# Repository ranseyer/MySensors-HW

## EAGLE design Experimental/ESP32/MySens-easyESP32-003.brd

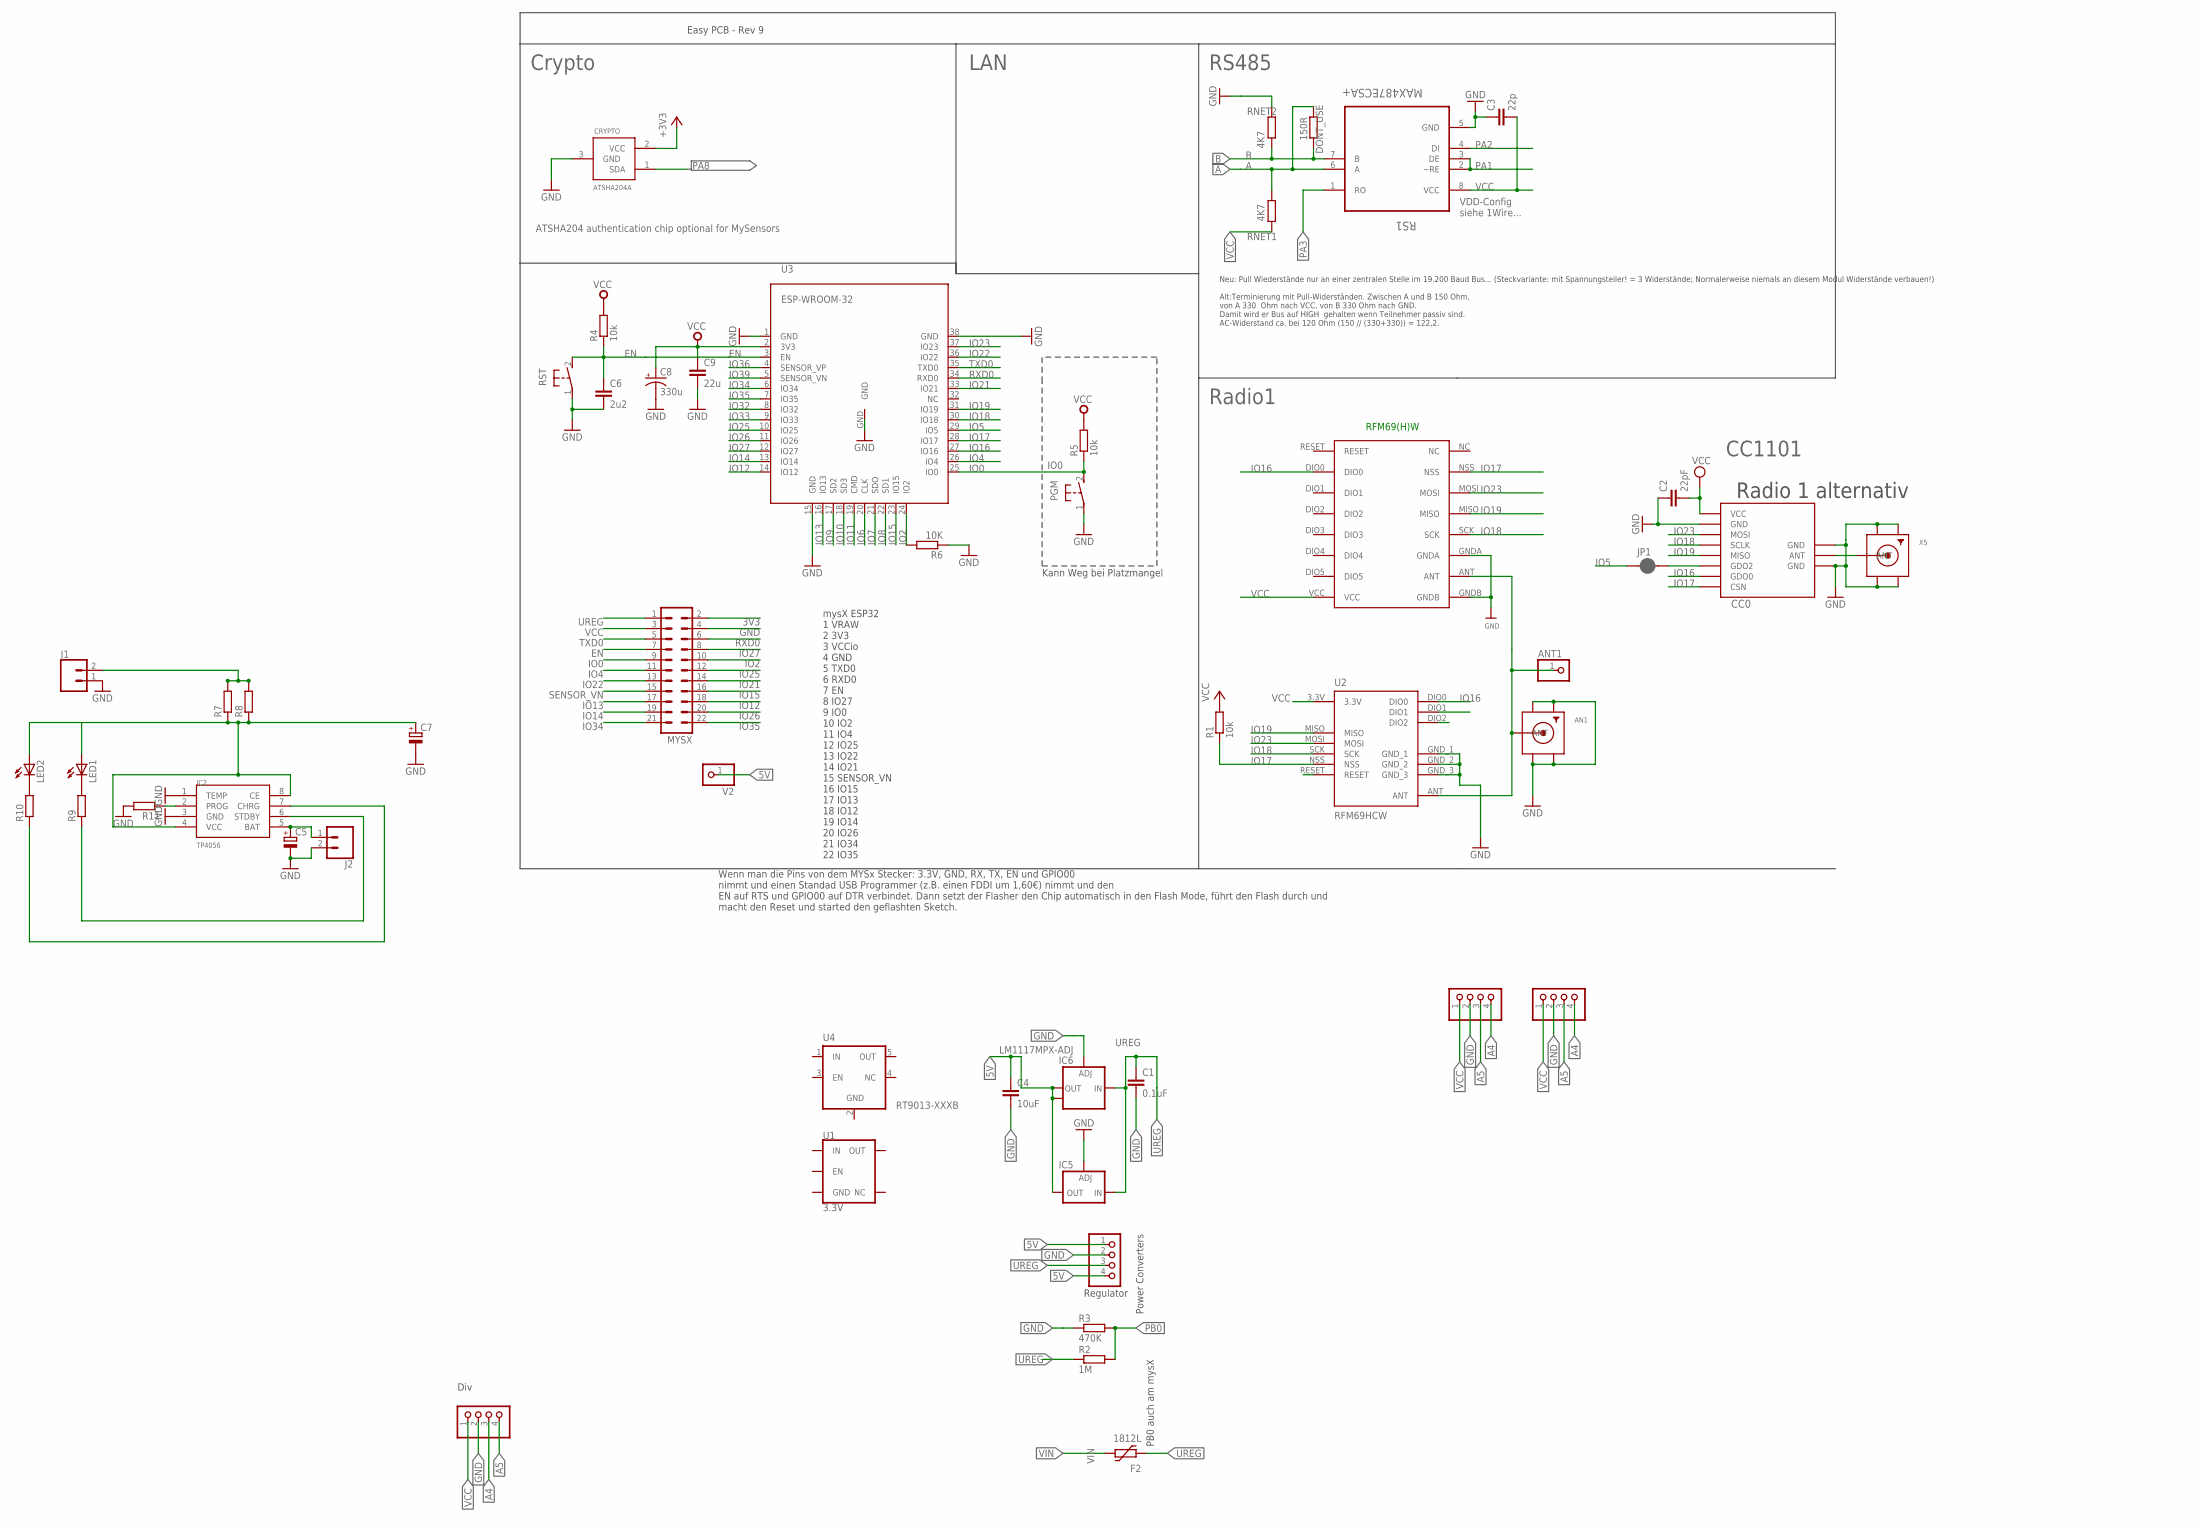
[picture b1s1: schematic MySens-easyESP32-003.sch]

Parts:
AN1: SMACONNECTOR_EDGE; SMA_EDGELAUNCH
ANT1: PINHD-1X1; 1X01
BH1750: PINHD-1X04_2.54-S; 1X04-S
C1: 0.1uF; C1206
C2: 22pF; C0805
C3: 22p; C0805
C4: 10uF; C1210
C5, C7: CPOL-EUE2.5-7; E2,5-7
C6: 2u2; C0603
C8: 330u; VISHAY_C
C9: 22u; 0805
CC0: CC1101; CC1101_MODULE1_SMD
CRYPTO: ATSHA204A; SOT23
DONT_USE: 150R; R0805
F2: 1812L
I2C-1, I2C-2: PINHD-1X04_2.54-S; 1X04-S
IC2: TP4056; SOP-8
IC5: LD117ADT50TR; DPACK
IC6: LM1117MPX-ADJ; SOT223
J1, J2: CONN_02PTH4; 1X02_XTRA_BIG
JP1: JUMPER-SMT_2_NC_PASTE_NO-SILK; SMT-JUMPER_2_NC_PASTE_NO-SILK
LED1, LED2: LED5MM
MYSX: MA11-2
PGM: DTSM-3
R1: 10k; M0805
R2: 1M; R0805
R3: 470K; R0805
R4, R5: 10k; R0603
R6: 10K; R0603
R7, R8, R9, R10, R11: R-EU_R1206; R1206
RFM69W1: RFM69HW; RFM
RNET1, RNET2: 4K7; R0805
RS1: MAX487ECSA+; SOIC127P600X175-8N
RST: DTSM-3
STEPDWN: PINHD-1X04_2.54-S; 1X04-S
U1: 3.3V; SOT23-5
U2: RFM69HCW; RFM69HCW-XXXS2
U3: ESP-WROOM-32
U4: RT9013-XXXB; SOT23-5
V2: PINHD-1X1; 1X01
X5: SMACONNECTOR_EDGE; SMA_EDGELAUNCH

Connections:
3V3: CRYPTO.2 (VCC), MYSX.2
5V: C4.1, IC5.4 (OUT), IC6.2 (OUT), IC6.TAB (OUT1), STEPDWN.1, STEPDWN.4, V2.1
A: DONT_USE.1, RNET1.2, RS1.6 (A)
A4: BH1750.4, I2C-1.4, I2C-2.3
A5: BH1750.3, I2C-1.3, I2C-2.4
ANT0: CC0.ANT, X5.P (ANT)
ANT1: AN1.P (ANT), ANT1.1, RFM69W1.ANT, U2.ANT
B: DONT_USE.2, RNET2.1, RS1.7 (B)
EN: C6.1, MYSX.7, R4.1, RST.2, U3.3 (EN)
GND: AN1.GND@1 (GND4), AN1.GND@2 (GND3), AN1.GND@3 (GND2), AN1.GND@4 (GND1), BH1750.2, C1.2, C2.1, C3.1, C4.2, C5.-, C6.2, C7.-, C8.-, C9.2, CC0.GND@0 (GND), CC0.GND@1 (GND), CC0.GND@2 (GND), CRYPTO.3 (GND), I2C-1.2, I2C-2.2, IC2.1 (TEMP), IC2.3 (GND), IC5.1 (ADJ), IC6.1 (ADJ), J1.1, J2.2, MYSX.4, PGM.1, R3.1, R6.1, R11.2, RFM69W1.GNDA, RFM69W1.GNDB, RNET2.2, RS1.5 (GND), RST.1, STEPDWN.2, U2.GND_1, U2.GND_2, U2.GND_3, U3.1 (GND), U3.15 (GND), U3.38 (GND), U3.GND, U4.2 (GND), X5.GND@1 (GND4), X5.GND@2 (GND3), X5.GND@3 (GND2), X5.GND@4 (GND1)
IO0: MYSX.9, PGM.2, R5.1, U3.25 (IO0)
IO2: MYSX.10, R6.2, U3.24 (IO2)
IO4: MYSX.11, U3.26 (IO4)
IO5: JP1.1, U3.29 (IO5)
IO6: U3.20 (CLK)
IO7: U3.21 (SDO)
IO8: U3.22 (SD1)
IO9: U3.17 (SD2)
IO10: U3.18 (SD3)
IO11: U3.19 (CMD)
IO12: MYSX.18, U3.14 (IO12)
IO13: MYSX.17, U3.16 (IO13)
IO14: MYSX.19, U3.13 (IO14)
IO15: MYSX.16, U3.23 (IO15)
IO16: CC0.GDO0, RFM69W1.DIO0, U2.DIO0, U3.27 (IO16)
IO17: CC0.CSN, R1.1, RFM69W1.NSS, U2.NSS, U3.28 (IO17)
IO18: CC0.SCLK, RFM69W1.SCK, U2.SCK, U3.30 (IO18)
IO19: CC0.MISO, RFM69W1.MISO, U2.MISO, U3.31 (IO19)
IO21: MYSX.14, U3.33 (IO21)
IO22: MYSX.13, U3.36 (IO22)
IO23: CC0.MOSI, RFM69W1.MOSI, U2.MOSI, U3.37 (IO23)
IO25: MYSX.12, U3.10 (IO25)
IO26: MYSX.20, U3.11 (IO26)
IO27: MYSX.8, U3.12 (IO27)
IO32: U3.8 (IO32)
IO33: U3.9 (IO33)
IO34: MYSX.21, U3.6 (IO34)
IO35: MYSX.22, U3.7 (IO35)
IO36: U3.4 (SENSOR_VP)
IO39: U3.5 (SENSOR_VN)
MAYBE_IO5: CC0.GDO2, JP1.2
unnamed: LED2.K (C), R10.2
unnamed: LED1.K (C), R9.2
unnamed: C5.+, IC2.5 (BAT), J2.1
unnamed: J1.2, R7.2, R8.2
unnamed: C7.+, IC2.4 (VCC), IC2.8 (CE), LED1.A, LED2.A, R7.1, R8.1
unnamed: IC2.6 (STDBY), R9.1
unnamed: IC2.7 (CHRG), R10.1
unnamed: IC2.2 (PROG), R11.1
PA1: RS1.2 (~RE), RS1.3 (DE)
PA2: RS1.4 (DI)
PA3: RS1.1 (RO)
PA8: CRYPTO.1 (SDA)
PB0: R2.2, R3.2
RXD0: MYSX.6, U3.34 (RXD0)
SENSOR_VN: MYSX.15
TXD0: MYSX.5, U3.35 (TXD0)
UREG: C1.1, F2.P$1 (1), IC5.3 (IN), IC6.3 (IN), MYSX.1, R2.1, STEPDWN.3
VCC: BH1750.1, C2.2, C3.2, C8.+, C9.1, CC0.VCC, I2C-1.1, I2C-2.1, MYSX.3, R1.2, R4.2, R5.2, RFM69W1.VCC, RNET1.1, RS1.8 (VCC), U2.3.3V, U3.2 (3V3)
VIN: F2.P$2 (2)

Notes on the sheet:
Easy PCB - Rev 9
ATSHA204 authentication chip optional for MySensors
VDD-Config siehe 1Wire...
Neu: Pull Wiederstände nur an einer zentralen Stelle im 19.200 Baud Bus... (Steckvariante: mit Spannungsteiler! = 3 Widerstände; Normalerweise niemals an diesem Modul Widerstände verbauen!) Alt:Terminierung mit Pull-Widerständen. Zwischen A und B 150 Ohm, von A 330 Ohm nach VCC, von B 330 Ohm nach 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
RFM69(H)W
Power Converters
Regulator
Div
mysX ESP32 1 VRAW 2 3V3 3 VCCio 4 GND 5 TXD0 6 RXD0 7 EN 8 IO27 9 IO0 10 IO2 11 IO4 12 IO25 13 IO22 14 IO21 15 SENSOR_VN 16 IO15 17 IO13 18 IO12 19 IO14 20 IO26 21 IO34 22 IO35
PB0 auch am mysX
Radio1
LAN
RS485
Crypto
Radio 1 alternativ
CC1101
Kann Weg bei Platzmangel
Wenn man die Pins von dem MYSx Stecker: 3.3V, GND, RX, TX, EN und GPIO00 nimmt und einen Standad USB Programmer (z.B. einen FDDI um 1,60€) nimmt und den EN auf RTS und GPIO00 auf DTR verbindet. Dann setzt der Flasher den Chip automatisch in den Flash Mode, führt den Flash durch und macht den Reset 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

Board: 2 copper layers, 51 parts (16 on the bottom side), 45 nets, no tracks yet.

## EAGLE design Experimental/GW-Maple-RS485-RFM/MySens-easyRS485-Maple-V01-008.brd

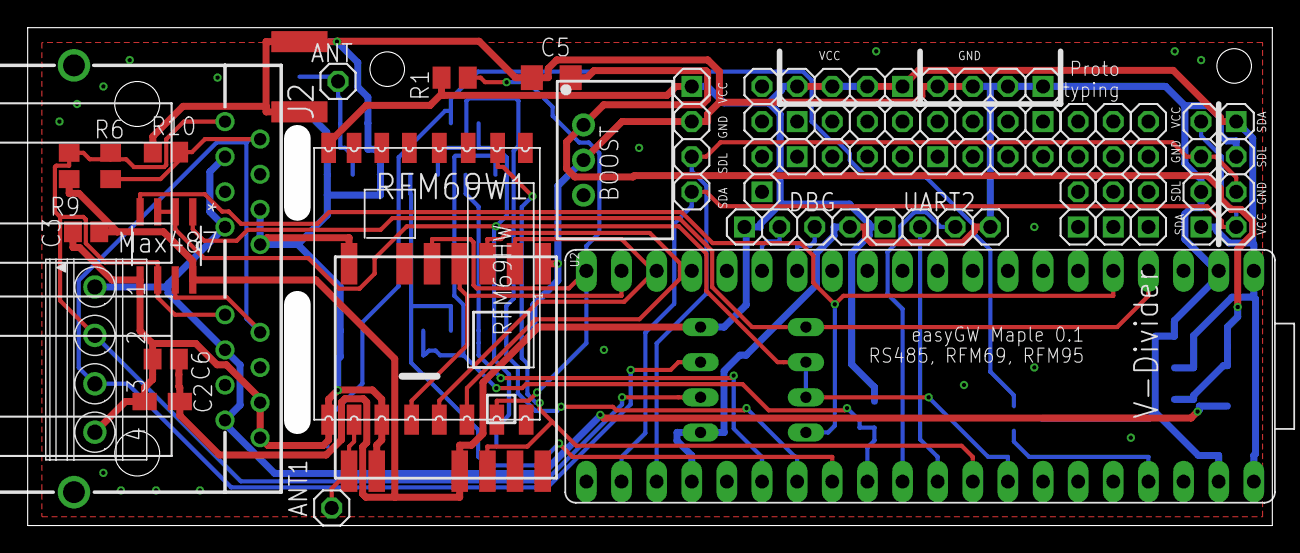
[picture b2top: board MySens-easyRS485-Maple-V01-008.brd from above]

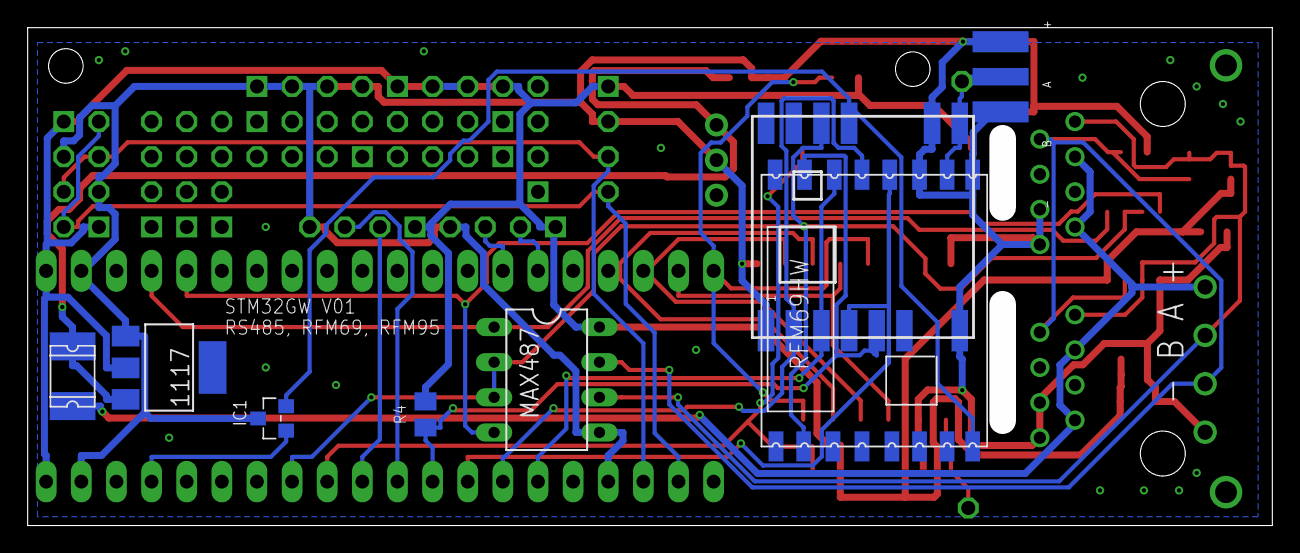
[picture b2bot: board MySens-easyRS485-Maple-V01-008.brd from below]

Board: 2 copper layers, 90.0 x 36.0 mm, 40 parts (8 on the bottom side), 28 nets.

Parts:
1117: REG1117; SOT223
ANT, ANT1: 1X01
BOOST: R-78C1.8-1.0; SIP3
C2: 10uF; R/2012-12W
C3: 22p; C0805
C5: 0.1uF; C1206
C6: 22pF; C0805
DBG: 1X04-S
F1: 1812L
IC1: ATSHA204A; SOT23
J2: 557570-1
JP1, JP2, JP3, JP4, JP5, JP6, JP7, JP8, JP9, JP10, JP11, JP12, JP15: 1X04-S
MAX487: MAX481CPA; DIL08
R1, R4: 10k; M0805
R6: 150R; R0805
R9, R10: 330R; R0805
RFM69W, RFM69W1: RFM69HW; RFM
RS1: MAX487ECSA+; SOIC127P600X175-8N
U1, U2: RFM69HCW; RFM69HCW-XXXS2
U$2: MAPLEMINI; 20-DIP
UART2: 1X04-S
X2: SMA_EDGELAUNCH
X3: 1751264

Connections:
3V3: IC1.2, RFM69W.VCC, U1.3.3V
A: J2.1-1, J2.2-1, MAX487.6, R6.1, R9.2, RS1.6, X3.2
ANT: ANT.1, RFM69W.ANT, U1.ANT, X2.P
ANT1: ANT1.1, RFM69W1.ANT, U2.ANT
B: J2.1-2, J2.2-2, MAX487.7, R6.2, R10.1, RS1.7, X3.3
B6_TX: MAX487.4, RS1.4, U$2.5
B7_RX: MAX487.1, RS1.1, U$2.4
CSN: R4.1, RFM69W.NSS, U1.NSS, U$2.29
CSN2: R1.1, RFM69W1.NSS, U2.NSS, U$2.20
GND: 1117.1, BOOST.2, C2.-, C3.1, C5.2, C6.2, DBG.4, IC1.3, J2.1-6, J2.1-8, J2.2-6, J2.2-8, JP1.1, JP1.2, JP1.3, JP1.4, JP2.2, JP5.2, JP10.2, MAX487.5, R10.2, RFM69W.GNDA, RFM69W.GNDB, RFM69W1.GNDA, RFM69W1.GNDB, RS1.5, U1.GND_1, U1.GND_2, U1.GND_3, U2.GND_1, U2.GND_2, U2.GND_3, U$2.2, U$2.24, U$2.39, UART2.4, X2.GND@1, X2.GND@2, X2.GND@3, X2.GND@4, X3.4
IN: F1.P$1, J2.1-3, J2.1-7, J2.2-3, J2.2-7, X3.1
IRQ: MAX487.2, MAX487.3, RFM69W.DIO0, RS1.2, RS1.3, U1.DIO0, U$2.33
IRQ2: RFM69W1.DIO0, U2.DIO0, U$2.32
MISO: RFM69W.MISO, U1.MISO, U$2.27
MISO2: RFM69W1.MISO, U2.MISO, U$2.18
MOSI: RFM69W.MOSI, U1.MOSI, U$2.26
MOSI2: RFM69W1.MOSI, U2.MOSI, U$2.17
PC13: IC1.1, U$2.37
RX-MAPLE: U$2.30, UART2.3
RX_DBG: DBG.3, U$2.14
SCK: RFM69W.SCK, U1.SCK, U$2.28
SCK2: RFM69W1.SCK, U2.SCK, U$2.19
SCL: JP2.3, JP5.3, JP10.3, U$2.23
SDA: JP2.4, JP5.4, JP10.4, U$2.22
TX-MAPLE: U$2.31, UART2.2
TX_DBG: DBG.2, U$2.15
VCC: 1117.2, C2.+, C3.2, C6.1, DBG.1, JP2.1, JP3.1, JP3.2, JP3.3, JP3.4, JP5.1, JP10.1, MAX487.8, R1.2, R4.2, R9.1, RFM69W1.VCC, RS1.8, U2.3.3V, U$2.1, U$2.40, UART2.1
VIN: 1117.3, BOOST.1, C5.1, F1.P$2

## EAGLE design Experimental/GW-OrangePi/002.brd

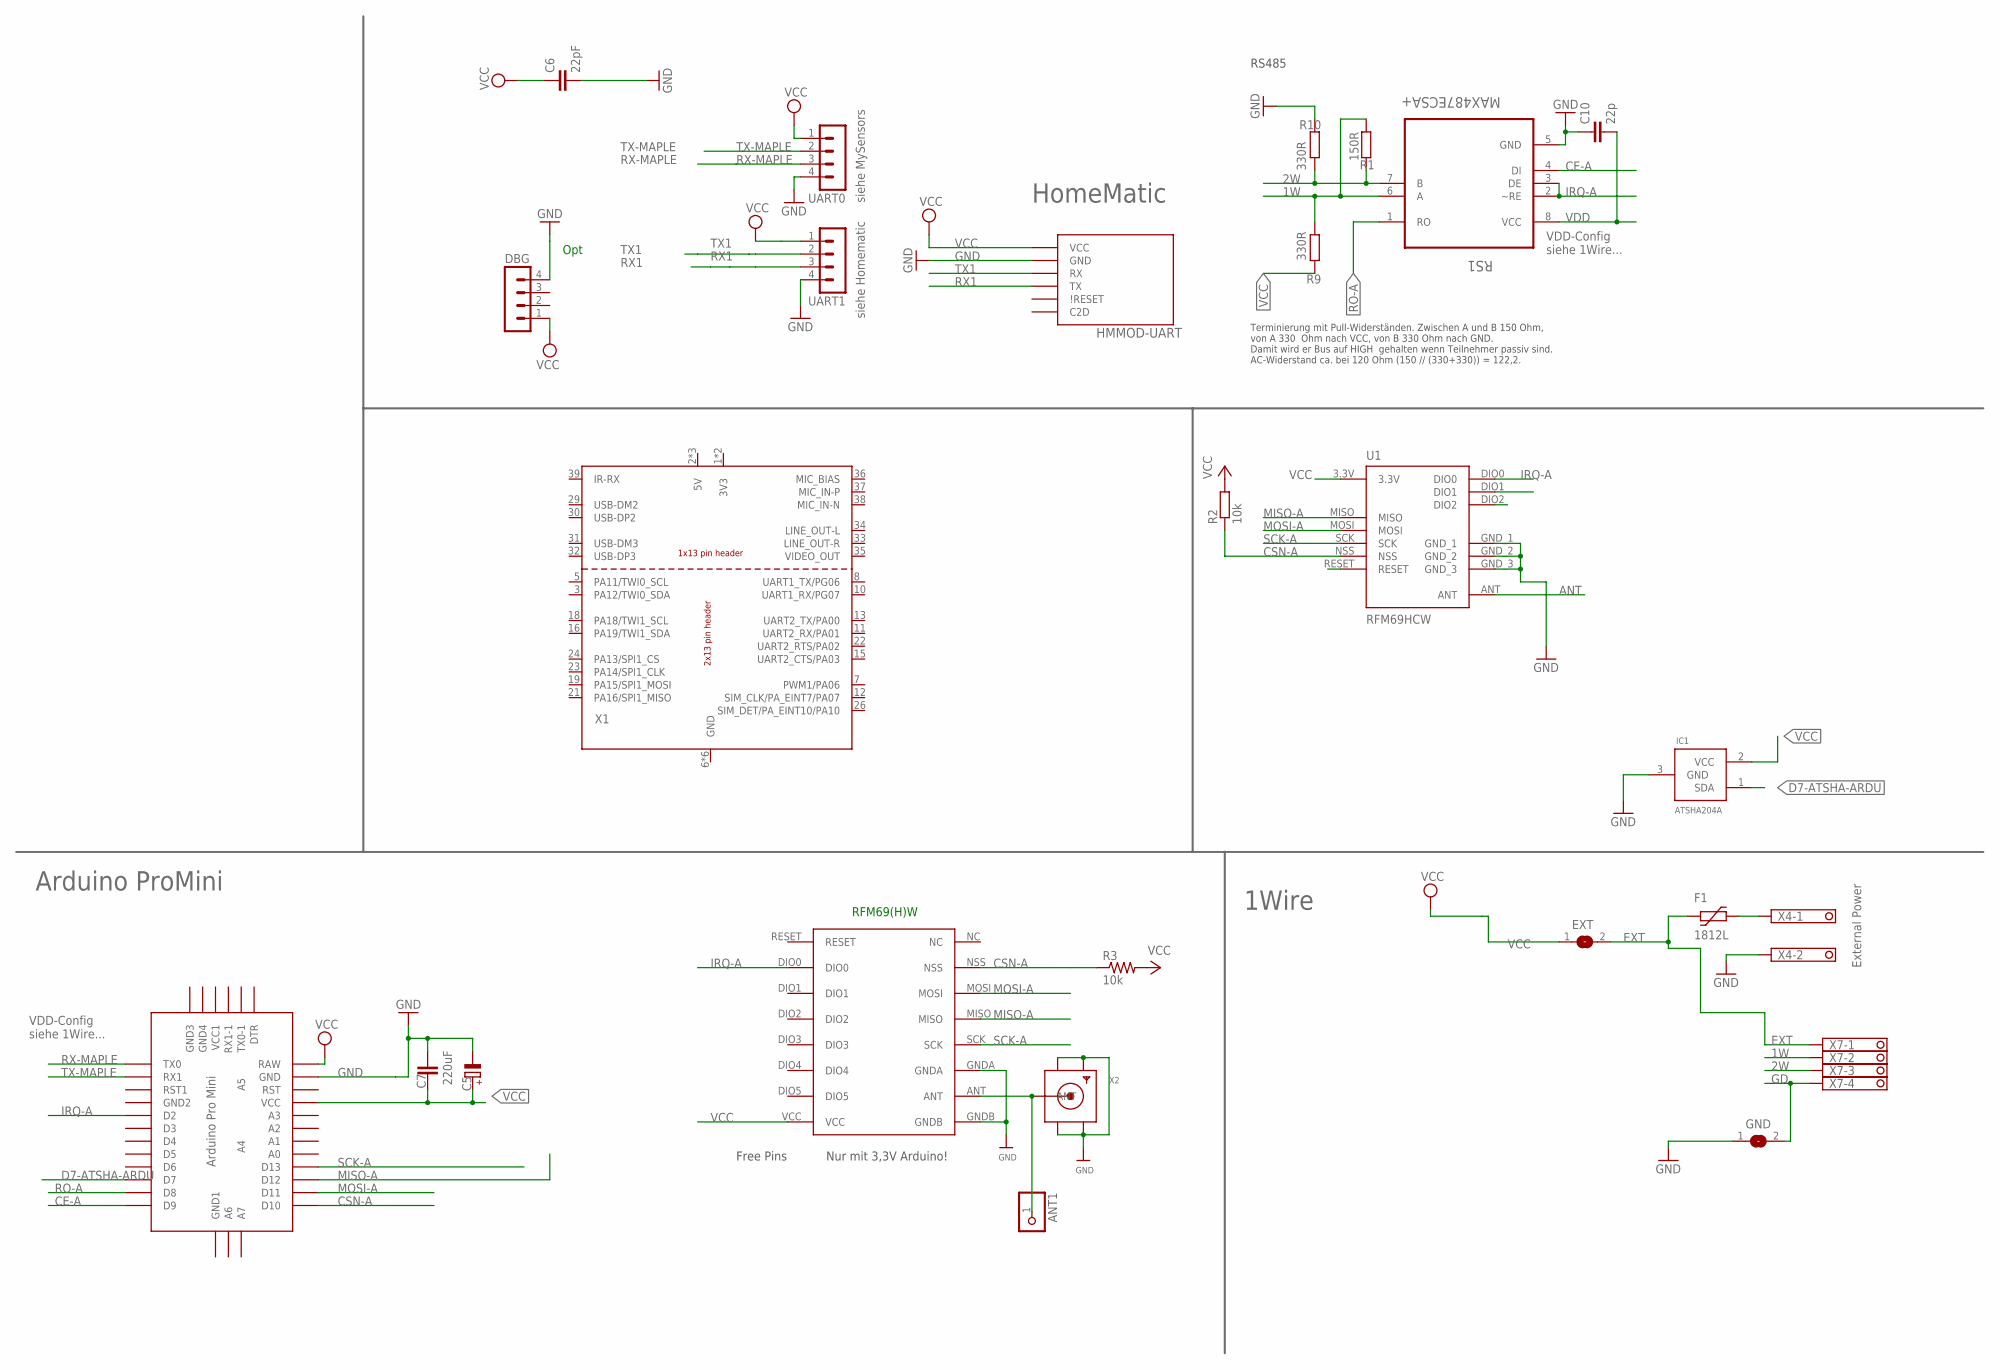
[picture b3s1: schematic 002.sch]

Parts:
ANT1: PINHD-1X1; 1X01
C5: 220uF; E5-8,5
C6: 22pF; C0805
C7: C-EUC1812; C1812
C10: 22p; C0805
DBG: MA04-1
EXT: SJ
F1: 1812L
GND: SJ
HMMOD-UART: HM-MOD-UARTDIL; HM-MOD-UART-DIL
IC1: ATSHA204A; SOT23
R1: 150R; R0805
R2: 10k; M0805
R3: 10k; 0805
R9, R10: 330R; R0805
RFM69W: RFM69HW; RFM
RS1: MAX487ECSA+; SOIC127P600X175-8N
U1: RFM69HCW; RFM69HCW-XXXS2
U$2: ABK-PRO-MINI
UART0, UART1: MA04-1
X1: OPI-ZERO-XHAT; OPI0HAT
X2: SMACONNECTOR_EDGE; SMA_EDGELAUNCH
X4: 1751248
X7: 1751264

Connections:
1W: R1.1, R9.2, RS1.6 (A), X7.2
2W: R1.2, R10.1, RS1.7 (B), X7.3
3V3: X1.1 (3V3), X1.17 (3V3)
5V: X1.2 (5V), X1.4 (5V), X1.27 (5V)
ANT: ANT1.1, RFM69W.ANT, U1.ANT, X2.P (ANT)
CE-A: RS1.4 (DI), U$2.D9
CSN-A: R2.1, R3.1, RFM69W.NSS, U1.NSS, U$2.D10
D7-ATSHA-ARDU: IC1.1 (SDA), U$2.D7
EXT: EXT.2, F1.P$1 (1), X7.1
GD: GND.2, X7.4
GND: C5.-, C6.2, C7.1, C10.1, DBG.4, GND.1, HMMOD-UART.2 (GND), IC1.3 (GND), R10.2, RFM69W.GNDA, RFM69W.GNDB, RS1.5 (GND), U1.GND_1, U1.GND_2, U1.GND_3, U$2.GND, UART0.4, UART1.4, X1.6 (GND), X1.9 (GND), X1.14 (GND), X1.20 (GND), X1.25 (GND), X1.28 (GND), X2.GND@1 (GND4), X2.GND@2 (GND3), X2.GND@3 (GND2), X2.GND@4 (GND1), X4.2
IRQ-A: RFM69W.DIO0, RS1.2 (~RE), RS1.3 (DE), U1.DIO0, U$2.D2
MISO-A: RFM69W.MISO, U1.MISO, U$2.D12
MOSI-A: RFM69W.MOSI, U1.MOSI, U$2.D11
unnamed: F1.P$2 (2), X4.1
RO-A: RS1.1 (RO), U$2.D8
RX1: HMMOD-UART.5 (TX), UART1.3
RX-MAPLE: U$2.TX0, UART0.3
SCK-A: RFM69W.SCK, U1.SCK, U$2.D13
TX1: HMMOD-UART.6 (RX), UART1.2
TX-MAPLE: U$2.RX1, UART0.2
VCC: C5.+, C6.1, C7.2, DBG.1, EXT.1, HMMOD-UART.1 (VCC), IC1.2 (VCC), R2.2, R3.2, R9.1, RFM69W.VCC, U1.3.3V, U$2.RAW, U$2.VCC, UART0.1, UART1.1
VDD: C10.2, RS1.8 (VCC)

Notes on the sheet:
Opt
siehe Homematic
siehe MySensors
HomeMatic
Arduino ProMini
VDD-Config siehe 1Wire...
RS485
Terminierung mit Pull-Widerständen. Zwischen A und B 150 Ohm, von A 330 Ohm nach VCC, von B 330 Ohm nach GND. Damit wird er Bus auf HIGH gehalten wenn Teilnehmer passiv sind. AC-Widerstand ca. bei 120 Ohm (150 // (330+330)) = 122,2.
1Wire
External Power
Free Pins
RFM69(H)W
Nur mit 3,3V Arduino!

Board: 2 copper layers, 26 parts (11 on the bottom side), 23 nets, no tracks yet.

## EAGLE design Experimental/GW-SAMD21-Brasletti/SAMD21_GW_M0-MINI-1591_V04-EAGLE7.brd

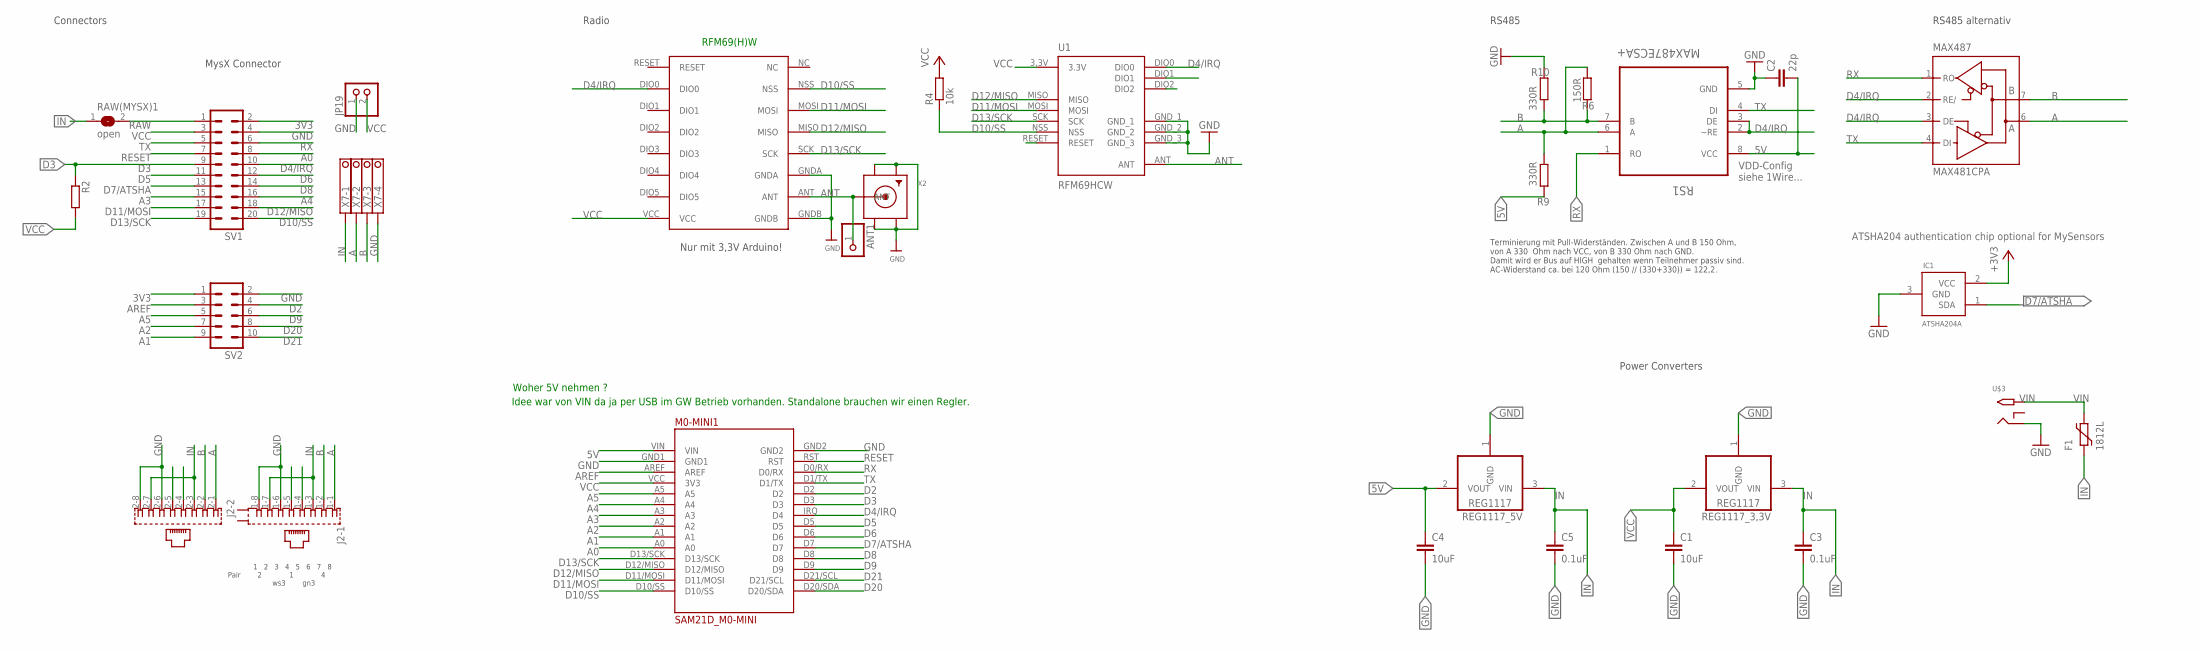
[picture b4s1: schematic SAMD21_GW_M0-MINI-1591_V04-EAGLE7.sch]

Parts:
ANT1: PINHD-1X1; 1X01
C1, C4: 10uF; C1210
C2: 22p; C0805
C3, C5: 0.1uF; C1206
F1: 1812L
IC1: ATSHA204A; SOT23
J2: 557570-1
JP19: PINHD-1X2; 1X02
M0-MINI1: SAM21D_M0-MINI; SAMD21_M0-MINI
MAX487: MAX481CPA; DIL08
R2: R-EU_R0805; R0805
R4: 10k; M0805
R6: 150R; R0805
R9, R10: 330R; R0805
RAW(MYSX)1: open; SJ
REG1117_3,3V, REG1117_5V: REG1117; SOT223
RFM69W: RFM69HW; RFM
RS1: MAX487ECSA+; SOIC127P600X175-8N
SV1: MA10-2
SV2: MA05-2
U1: RFM69HCW; RFM69HCW-XXXS2
U$3: 2.1MMJACKTHM; PJ-102A
X2: SMACONNECTOR_EDGE; SMA_EDGELAUNCH
X7: 1751264

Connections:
3V3: SV1.2, SV2.1
5V: C2.2, C4.1, M0-MINI1.VIN, R9.1, REG1117_5V.2 (VOUT), RS1.8 (VCC)
A: J2.1-1 (1), J2.2-1 (1), MAX487.6 (A), R6.1, R9.2, RS1.6 (A), X7.2
A0: M0-MINI1.A0, SV1.8
A1: M0-MINI1.A1, SV2.9
A2: M0-MINI1.A2, SV2.7
A3: M0-MINI1.A3, SV1.15
A4: M0-MINI1.A4, SV1.16
A5: M0-MINI1.A5, SV2.5
ANT: ANT1.1, RFM69W.ANT, U1.ANT, X2.P (ANT)
AREF: M0-MINI1.AREF, SV2.3
B: J2.1-2 (2), J2.2-2 (2), MAX487.7 (B), R6.2, R10.1, RS1.7 (B), X7.3
D2: M0-MINI1.D2, SV2.4
D3: M0-MINI1.D3, R2.1, SV1.9
D4/IRQ: M0-MINI1.IRQ (D4), RFM69W.DIO0, RS1.2 (~RE), RS1.3 (DE), SV1.10, U1.DIO0
D5: M0-MINI1.D5, SV1.11
D6: M0-MINI1.D6, SV1.12
D7/ATSHA: IC1.1 (SDA), M0-MINI1.D7, SV1.13
D8: M0-MINI1.D8, SV1.14
D9: M0-MINI1.D9, SV2.6
D10/SS: M0-MINI1.D10/SS, R4.1, RFM69W.NSS, SV1.20, U1.NSS
D11/MOSI: M0-MINI1.D11/MOSI, RFM69W.MOSI, SV1.17, U1.MOSI
D12/MISO: M0-MINI1.D12/MISO, RFM69W.MISO, SV1.18, U1.MISO
D13/SCK: M0-MINI1.D13/SCK, RFM69W.SCK, SV1.19, U1.SCK
D20: SV2.8
D21: SV2.10
GND: C1.2, C2.1, C3.2, C4.2, C5.2, IC1.3 (GND), J2.1-6 (6), J2.1-8 (8), J2.2-6 (6), J2.2-8 (8), JP19.1, M0-MINI1.GND1, M0-MINI1.GND2, MAX487.5 (GND), R10.2, REG1117_3,3V.1 (GND), REG1117_5V.1 (GND), RFM69W.GNDA, RFM69W.GNDB, RS1.5 (GND), SV1.4, SV2.2, U1.GND_1, U1.GND_2, U1.GND_3, U$3.RING, X2.GND@1 (GND4), X2.GND@2 (GND3), X2.GND@3 (GND2), X2.GND@4 (GND1), X7.4
IN: C3.1, C5.1, F1.P$1 (1), J2.1-3 (3), J2.1-7 (7), J2.2-3 (3), J2.2-7 (7), RAW(MYSX)1.1, REG1117_3,3V.3 (VIN), REG1117_5V.3 (VIN), X7.1
RAW: RAW(MYSX)1.2, SV1.1
RESET: M0-MINI1.RST, SV1.7
RX: M0-MINI1.D0/RX, RS1.1 (RO), SV1.6
TX: M0-MINI1.D1/TX, RS1.4 (DI), SV1.5
VCC: C1.1, IC1.2 (VCC), JP19.2, M0-MINI1.VCC (3V3), MAX487.8 (VCC), R2.2, R4.2, REG1117_3,3V.2 (VOUT), RFM69W.VCC, SV1.3, U1.3.3V
VIN: F1.P$2 (2), U$3.TIP

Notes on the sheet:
RFM69(H)W
Nur mit 3,3V Arduino!
Radio
1 2 3 4 5 6 7 8 Pair 2 1 4 ws3 gn3
Power Converters
ATSHA204 authentication chip optional for MySensors
RS485
VDD-Config siehe 1Wire...
Terminierung mit Pull-Widerständen. Zwischen A und B 150 Ohm, von A 330 Ohm nach VCC, von B 330 Ohm nach GND. Damit wird er Bus auf HIGH gehalten wenn Teilnehmer passiv sind. AC-Widerstand ca. bei 120 Ohm (150 // (330+330)) = 122,2.
RS485 alternativ
Connectors
MysX Connector
Woher 5V nehmen ?
Idee war von VIN da ja per USB im GW Betrieb vorhanden. Standalone brauchen wir einen Regler.

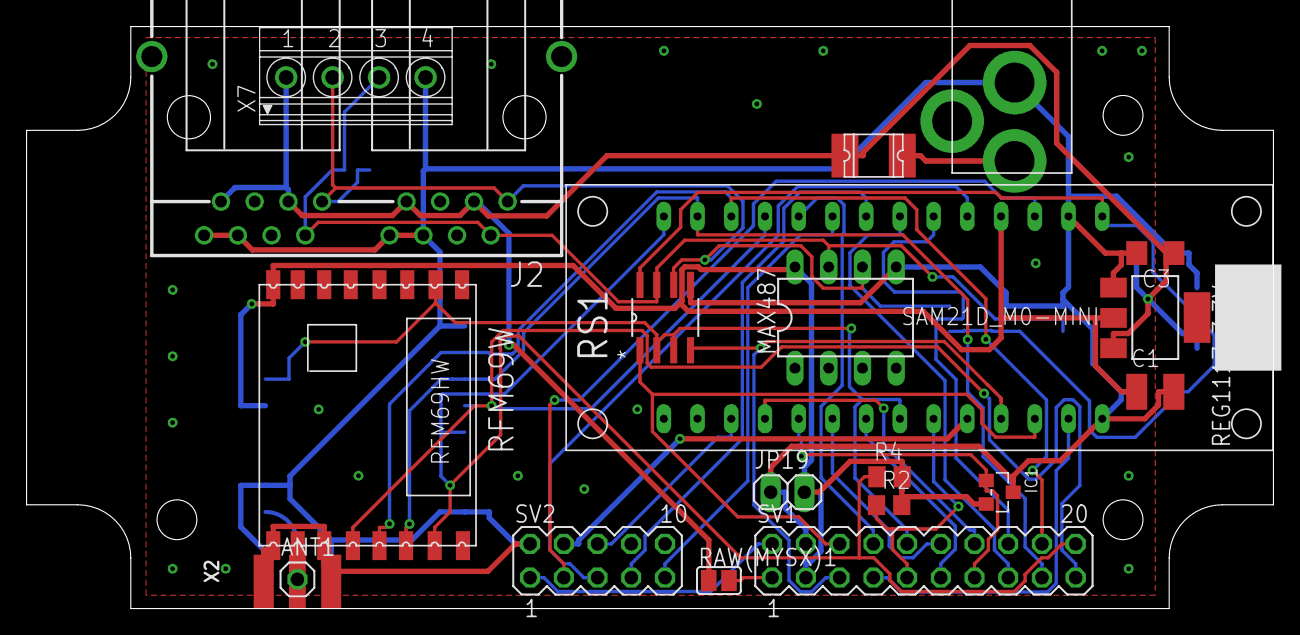
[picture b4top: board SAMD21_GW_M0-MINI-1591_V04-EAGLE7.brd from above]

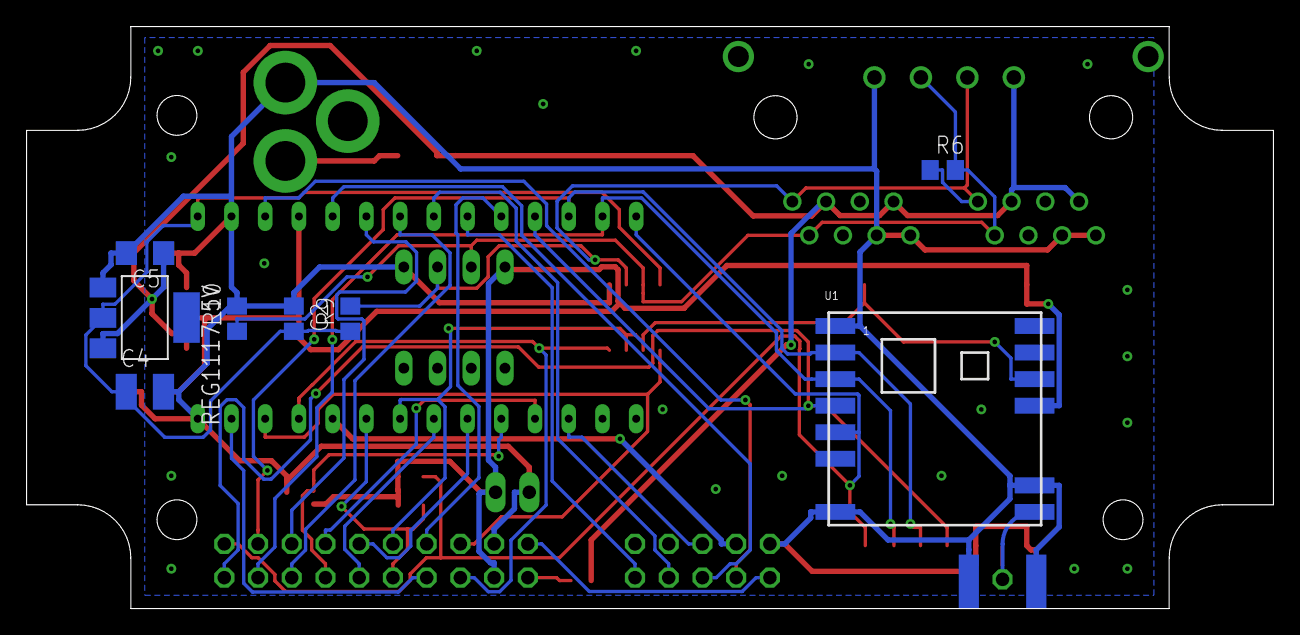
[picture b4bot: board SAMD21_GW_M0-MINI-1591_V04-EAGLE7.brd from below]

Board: 2 copper layers, 93.9 x 43.8 mm, 28 parts (8 on the bottom side), 32 nets.

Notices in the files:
parts and their libraries:
SparkFun-Passives: Licensing: Creative Commons ShareAlike 4.0 International - https://creativecommons.org/licenses/by-sa/4.0
microbuilder: This work is placed in the public domain, and may be freely used for commercial and non-commercial work with the following conditions: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
